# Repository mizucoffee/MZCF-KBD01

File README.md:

# MZCF-KBD01 V1 Rev.2

RP2040-Zero を搭載した分割キーボード。レイアウトは [ergogen](https://github.com/ergogen/ergogen) で生成し、KiCad 10 で設計しています。

## 構成

| パス | 内容 |
|---|---|
| `ergogen/` | ergogen 実行用ディレクトリ(レイアウト定義 `config.yaml`・カスタムフットプリント) |
| `pcb/` | KiCad プロジェクト(左: `MZCF-KBD01L.*`、右: `MZCF-KBD01R.*`)と部品ライブラリ |
| `cad/` | Plasticity 3D モデル |
| `firmware/` | QMK ファームウェア(キーボード定義・キーマップ) |
| `docs/` | ドキュメント用画像(キーマップレイアウト図) |

## 主要部品

- **MCU**: Waveshare RP2040-Zero(各手に1個)
- **ダイオード**: 1N4148W(SOD-123、裏面実装)
- **左右接続**: XH 2.54mm 4ピンコネクタ(5V / GND / GP28 / GP29)
- **スイッチ**: Cherry MX 互換(ソルダー)

## ファームウェア(QMK)

左右どちらの半分を USB 接続してもマスターとして動作します(EE_HANDS + SPLIT_USB_DETECT)。

ホスト OS を自動判別(QMK OS Detection)し、macOS / iOS 接続時は Alt と GUI を入れ替えたレイヤー(🌐 / Opt / Cmd の並び)に自動で切り替わります。それ以外(Windows / Linux / 判別不能時)は Windows 配列(Ctrl / Win / Alt)です。

Mac レイヤー左下の 🌐/fn キーは [tzarc/qmk_modules](https://github.com/tzarc/qmk_modules) の `globe_key` モジュール(コンシューマページ `AC Next Keyboard Layout Select` 0x029D を送信)によるもので、macOS に Globe キーとして認識されます。Apple 純正 fn の全機能(fn+矢印での PgUp/Home、fn+F キーの切り替え等)は再現されない簡易実装です。

### キーマップ

### ファームウェア構成

- 各半分に Waveshare RP2040-Zero(USB-C 搭載)
- マトリクス: COL0–8 = GP0–GP8 / ROW0–5 = GP9–GP14(COL2ROW、左右同一配線)
- 左右間通信: GP28 の単線ハーフデュプレックス(RP2040 PIO `vendor` ドライバ)。GP29 は予備
- ハンド判定ピンなし → EE_HANDS(初回書き込み時に EEPROM へ記録)

### セットアップ(初回のみ)

QMK CLI をインストールし、qmk_firmware を取得したうえで、`firmware/` を `mzcf_kbd01` という名前で symlink します(キーボード名は symlink 名で決まります)。

```sh
brew install qmk/qmk/qmk        # または pipx install qmk
qmk setup -H ~/qmk_firmware
ln -sfn "$(pwd)/firmware" ~/qmk_firmware/keyboards/mzcf_kbd01   # リポジトリ root で実行

# コミュニティモジュール(Mac用 🌐/fn キーに使用)
git clone https://github.com/tzarc/qmk_modules.git ~/qmk_firmware/modules/tzarc
```

※ QMK External Userspace はキーマップ専用でキーボード定義を置けないため、symlink 方式にしています。キーボード定義の実体はこのリポジトリで管理されます。

### ビルド

```sh
qmk compile -kb mzcf_kbd01 -km default
# → ~/qmk_firmware/mzcf_kbd01_default.uf2
```

### 書き込み

初回(左右のハンド情報を書き込む・各半分1回だけ):

```sh
# 左手側
qmk flash -kb mzcf_kbd01 -km default -bl uf2-split-left
# 右手側
qmk flash -kb mzcf_kbd01 -km default -bl uf2-split-right
```

ブートローダへの入り方: RP2040-Zero の **BOOT** ボタンを押しながら USB を接続すると `RPI-RP2` ドライブがマウントされ、qmk が自動で書き込みます(UF2 のドラッグ&ドロップでも可)。

2回目以降:

```sh
qmk flash -kb mzcf_kbd01 -km default -bl uf2
```

ハンド情報は EEPROM(フラッシュエミュレーション)に保持されるため、通常の書き込みでは消えません。`flash_nuke.uf2` などでフラッシュを全消去した場合のみ、初回手順をやり直してください。

### 運用メモ

- USB を接続した側が自動的にマスターになります(SPLIT_USB_DETECT。接続後 2 秒ほどの判定時間があります)
- もう一方の半分は TRRS 経由で給電・通信されます
- **TRRS ケーブルの活線挿抜はしないでください**(5V が通っているため。抜き差しは USB を抜いた状態で)
- Bootmagic は無効化しています(EEPROM リセットでハンド情報が消えるのを防ぐため)。ブートローダには BOOT ボタンで入ってください

## ライブラリについて

`pcb/libs/lcsc/` のシンボル・フットプリントは LCSC / EasyEDA のデータを変換したものです。

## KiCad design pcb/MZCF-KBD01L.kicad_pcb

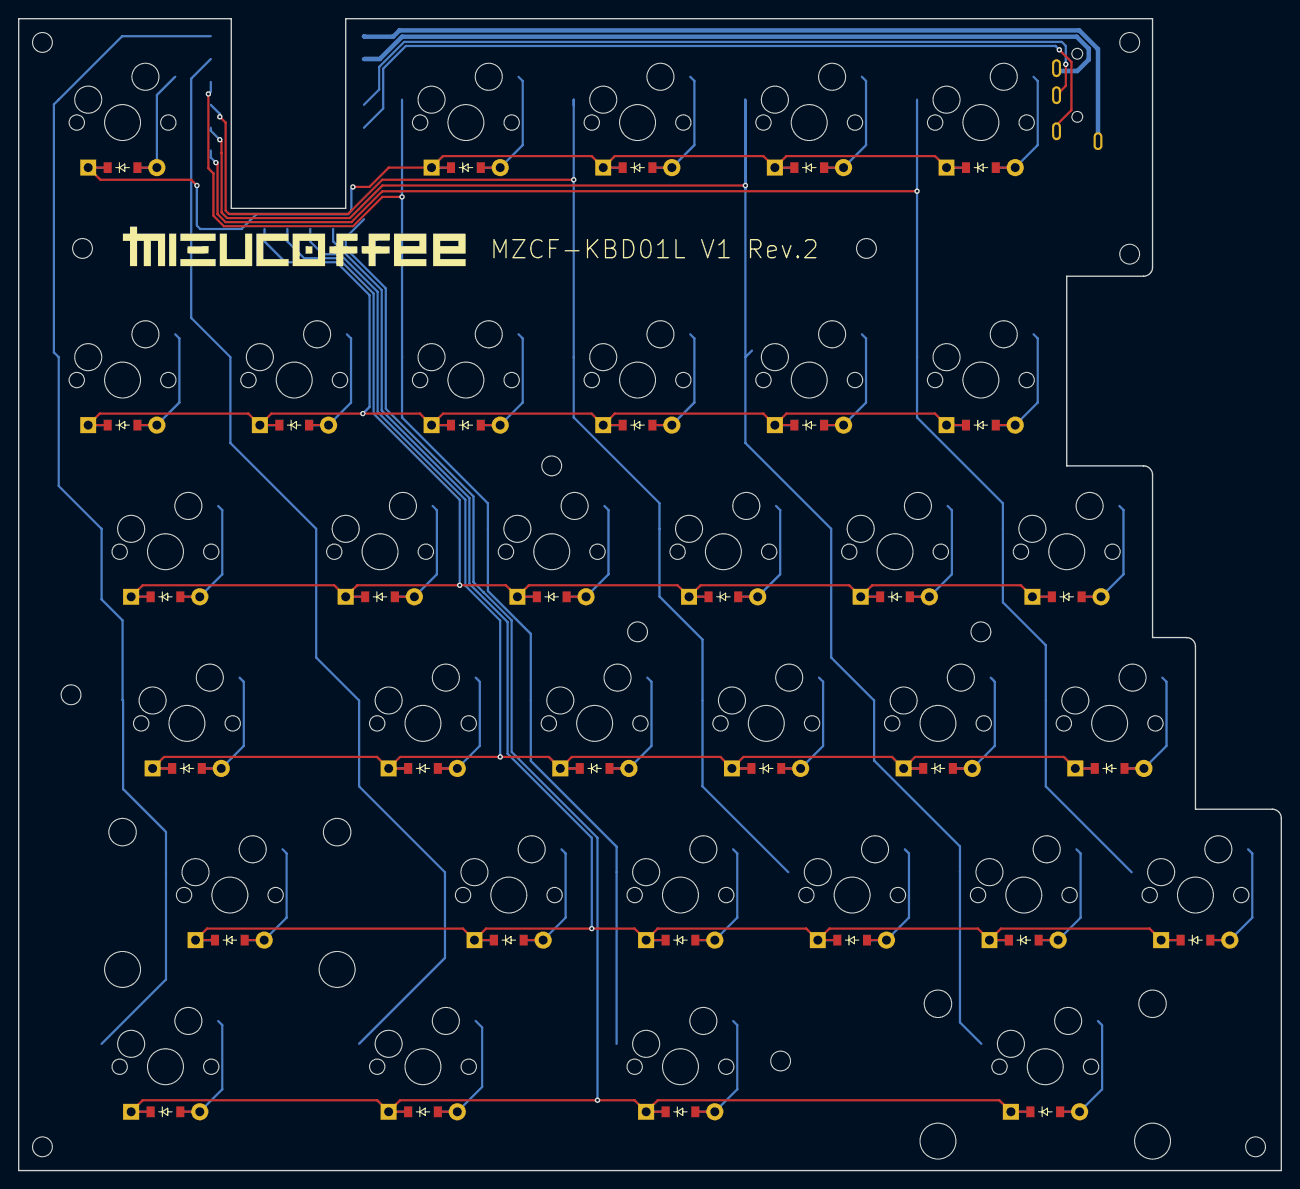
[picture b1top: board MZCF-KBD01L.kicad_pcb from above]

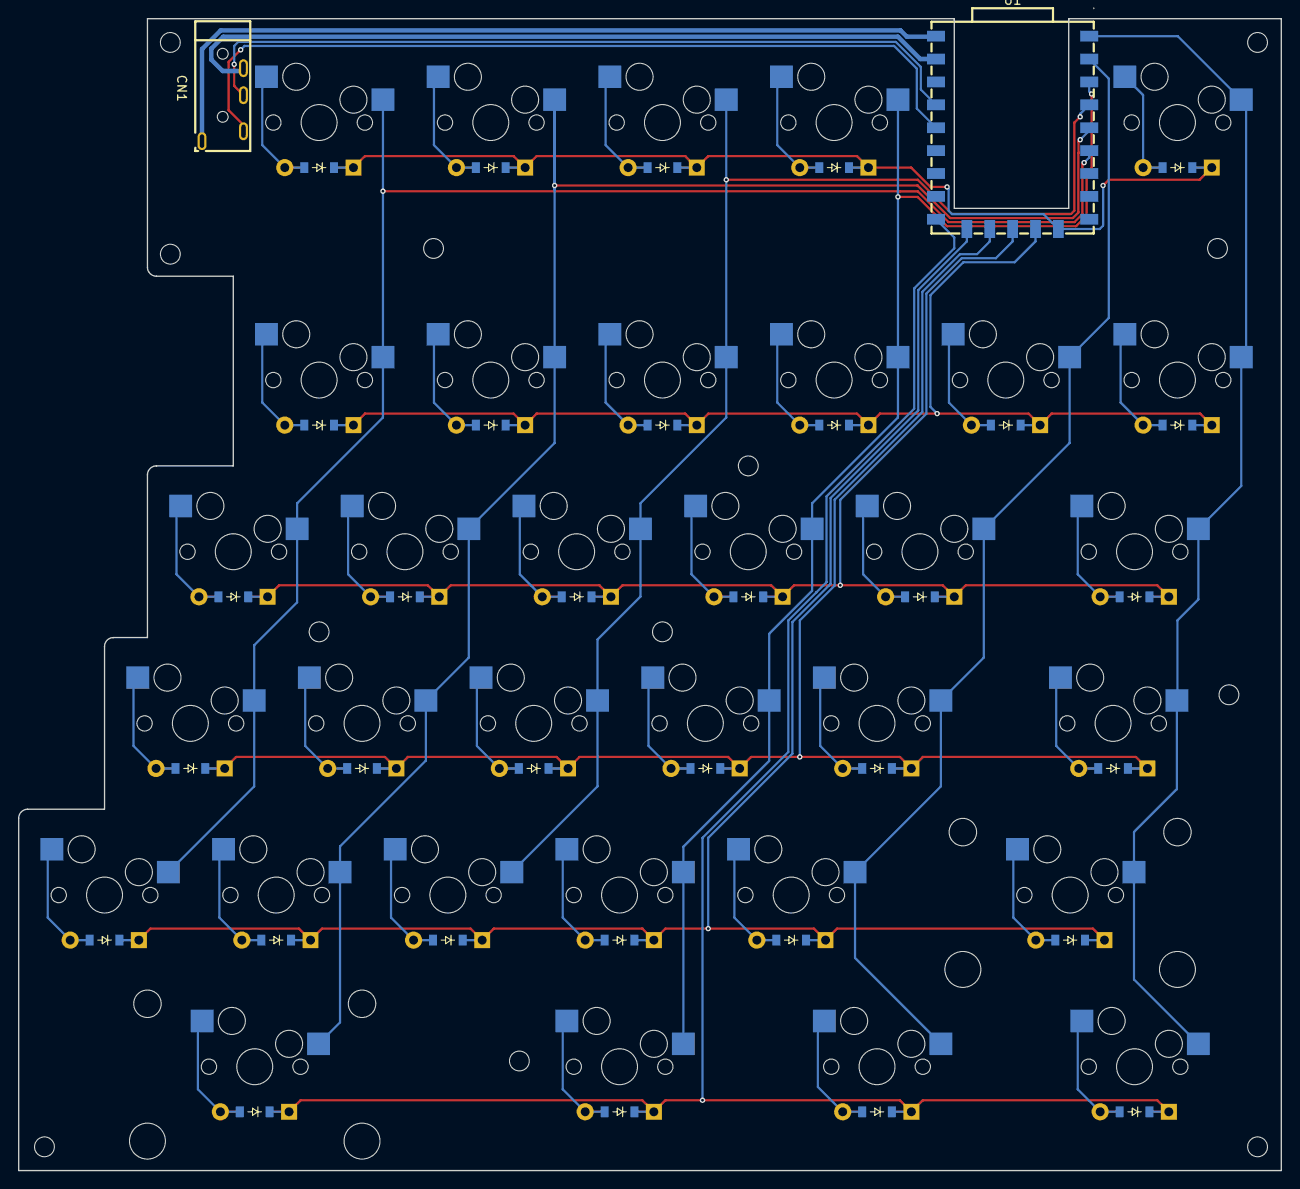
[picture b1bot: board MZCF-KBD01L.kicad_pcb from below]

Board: 2 copper layers, 140.1 x 127.8 mm, 82 parts (35 on the bottom side), 49 nets.

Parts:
CN1: PJ-320A_C49284721; C49284721_AUDIO-TH_PJ-320A_C49284721
D1, D2, D3, D4, D5, D6, D8, D9, D10, D11, D12, D13, D14, D15, D16, D17, D18, D19, D20, D21, D22, D23, D25, D26, D27, D28, D29, D30, D31, D32, D33, D34, D35: 1N4148W; ComboDiode
H1, H1#2, H1#3, H1#4, H1#5, H1#6, H1#7, H1#8, H1#9, H1#10, H1#11, H1#12: MountingHole_2.2mm_M2
ST1, ST2: STAB_MX
SW1, SW2, SW3, SW4, SW5, SW6, SW8, SW9, SW10, SW11, SW12, SW13, SW14, SW15, SW16, SW17, SW18, SW19, SW20, SW21, SW22, SW23, SW25, SW26, SW27, SW28, SW29, SW30, SW31, SW32, SW33, SW34, SW35: SW_Push; MX
U1: RP2040-ZERO; C5350143_COMM-SMD_RP2040-ZERO

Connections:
/COL0: SW1.1, SW2.1, SW3.1, SW4.1, SW5.1, SW6.1, U1.1 (GP0)
/COL1: SW8.1, SW9.1, SW10.1, SW11.1, SW12.1, U1.2 (GP1)
/COL2: SW13.1, SW14.1, SW15.1, SW16.1, SW17.1, SW18.1, U1.3 (GP2)
/COL3: SW19.1, SW20.1, SW21.1, SW22.1, SW23.1, U1.4 (GP3)
/COL4: SW25.1, SW26.1, SW27.1, SW28.1, SW29.1, SW30.1, U1.5 (GP4)
/COL5: SW31.1, SW32.1, SW33.1, SW34.1, SW35.1, U1.6 (GP5)
/ROW0: D1.1 (K), D13.1 (K), D19.1 (K), D25.1 (K), D31.1 (K), U1.10 (GP9)
/ROW1: D2.1 (K), D8.1 (K), D14.1 (K), D20.1 (K), D26.1 (K), D32.1 (K), U1.11 (GP10)
/ROW2: D3.1 (K), D9.1 (K), D15.1 (K), D21.1 (K), D27.1 (K), D33.1 (K), U1.12 (GP11)
/ROW3: D4.1 (K), D10.1 (K), D16.1 (K), D22.1 (K), D28.1 (K), D34.1 (K), U1.13 (GP12)
/ROW4: D5.1 (K), D11.1 (K), D17.1 (K), D23.1 (K), D29.1 (K), D35.1 (K), U1.14 (GP13)
/ROW5: D6.1 (K), D12.1 (K), D18.1 (K), D30.1 (K), U1.15 (GP14)
unnamed: D1.2 (A), SW1.2
unnamed: D2.2 (A), SW2.2
unnamed: D3.2 (A), SW3.2
unnamed: D4.2 (A), SW4.2
unnamed: D5.2 (A), SW5.2
unnamed: D6.2 (A), SW6.2
unnamed: D8.2 (A), SW8.2
unnamed: D9.2 (A), SW9.2
unnamed: D10.2 (A), SW10.2
unnamed: D11.2 (A), SW11.2
unnamed: D12.2 (A), SW12.2
unnamed: D13.2 (A), SW13.2
unnamed: D14.2 (A), SW14.2
unnamed: D15.2 (A), SW15.2
unnamed: D16.2 (A), SW16.2
unnamed: D17.2 (A), SW17.2
unnamed: D18.2 (A), SW18.2
unnamed: D19.2 (A), SW19.2
unnamed: D20.2 (A), SW20.2
unnamed: D21.2 (A), SW21.2
unnamed: D22.2 (A), SW22.2
unnamed: D23.2 (A), SW23.2
unnamed: D25.2 (A), SW25.2
unnamed: D26.2 (A), SW26.2
unnamed: D27.2 (A), SW27.2
unnamed: D28.2 (A), SW28.2
unnamed: D29.2 (A), SW29.2
unnamed: D30.2 (A), SW30.2
unnamed: D31.2 (A), SW31.2
unnamed: D32.2 (A), SW32.2
unnamed: D33.2 (A), SW33.2
unnamed: D34.2 (A), SW34.2
unnamed: D35.2 (A), SW35.2
unnamed: CN1.2, U1.23 (5V)
unnamed: CN1.5, U1.22 (GND)
unnamed: CN1.4, U1.19 (GP28)
unnamed: CN1.3, U1.20 (GP29)
